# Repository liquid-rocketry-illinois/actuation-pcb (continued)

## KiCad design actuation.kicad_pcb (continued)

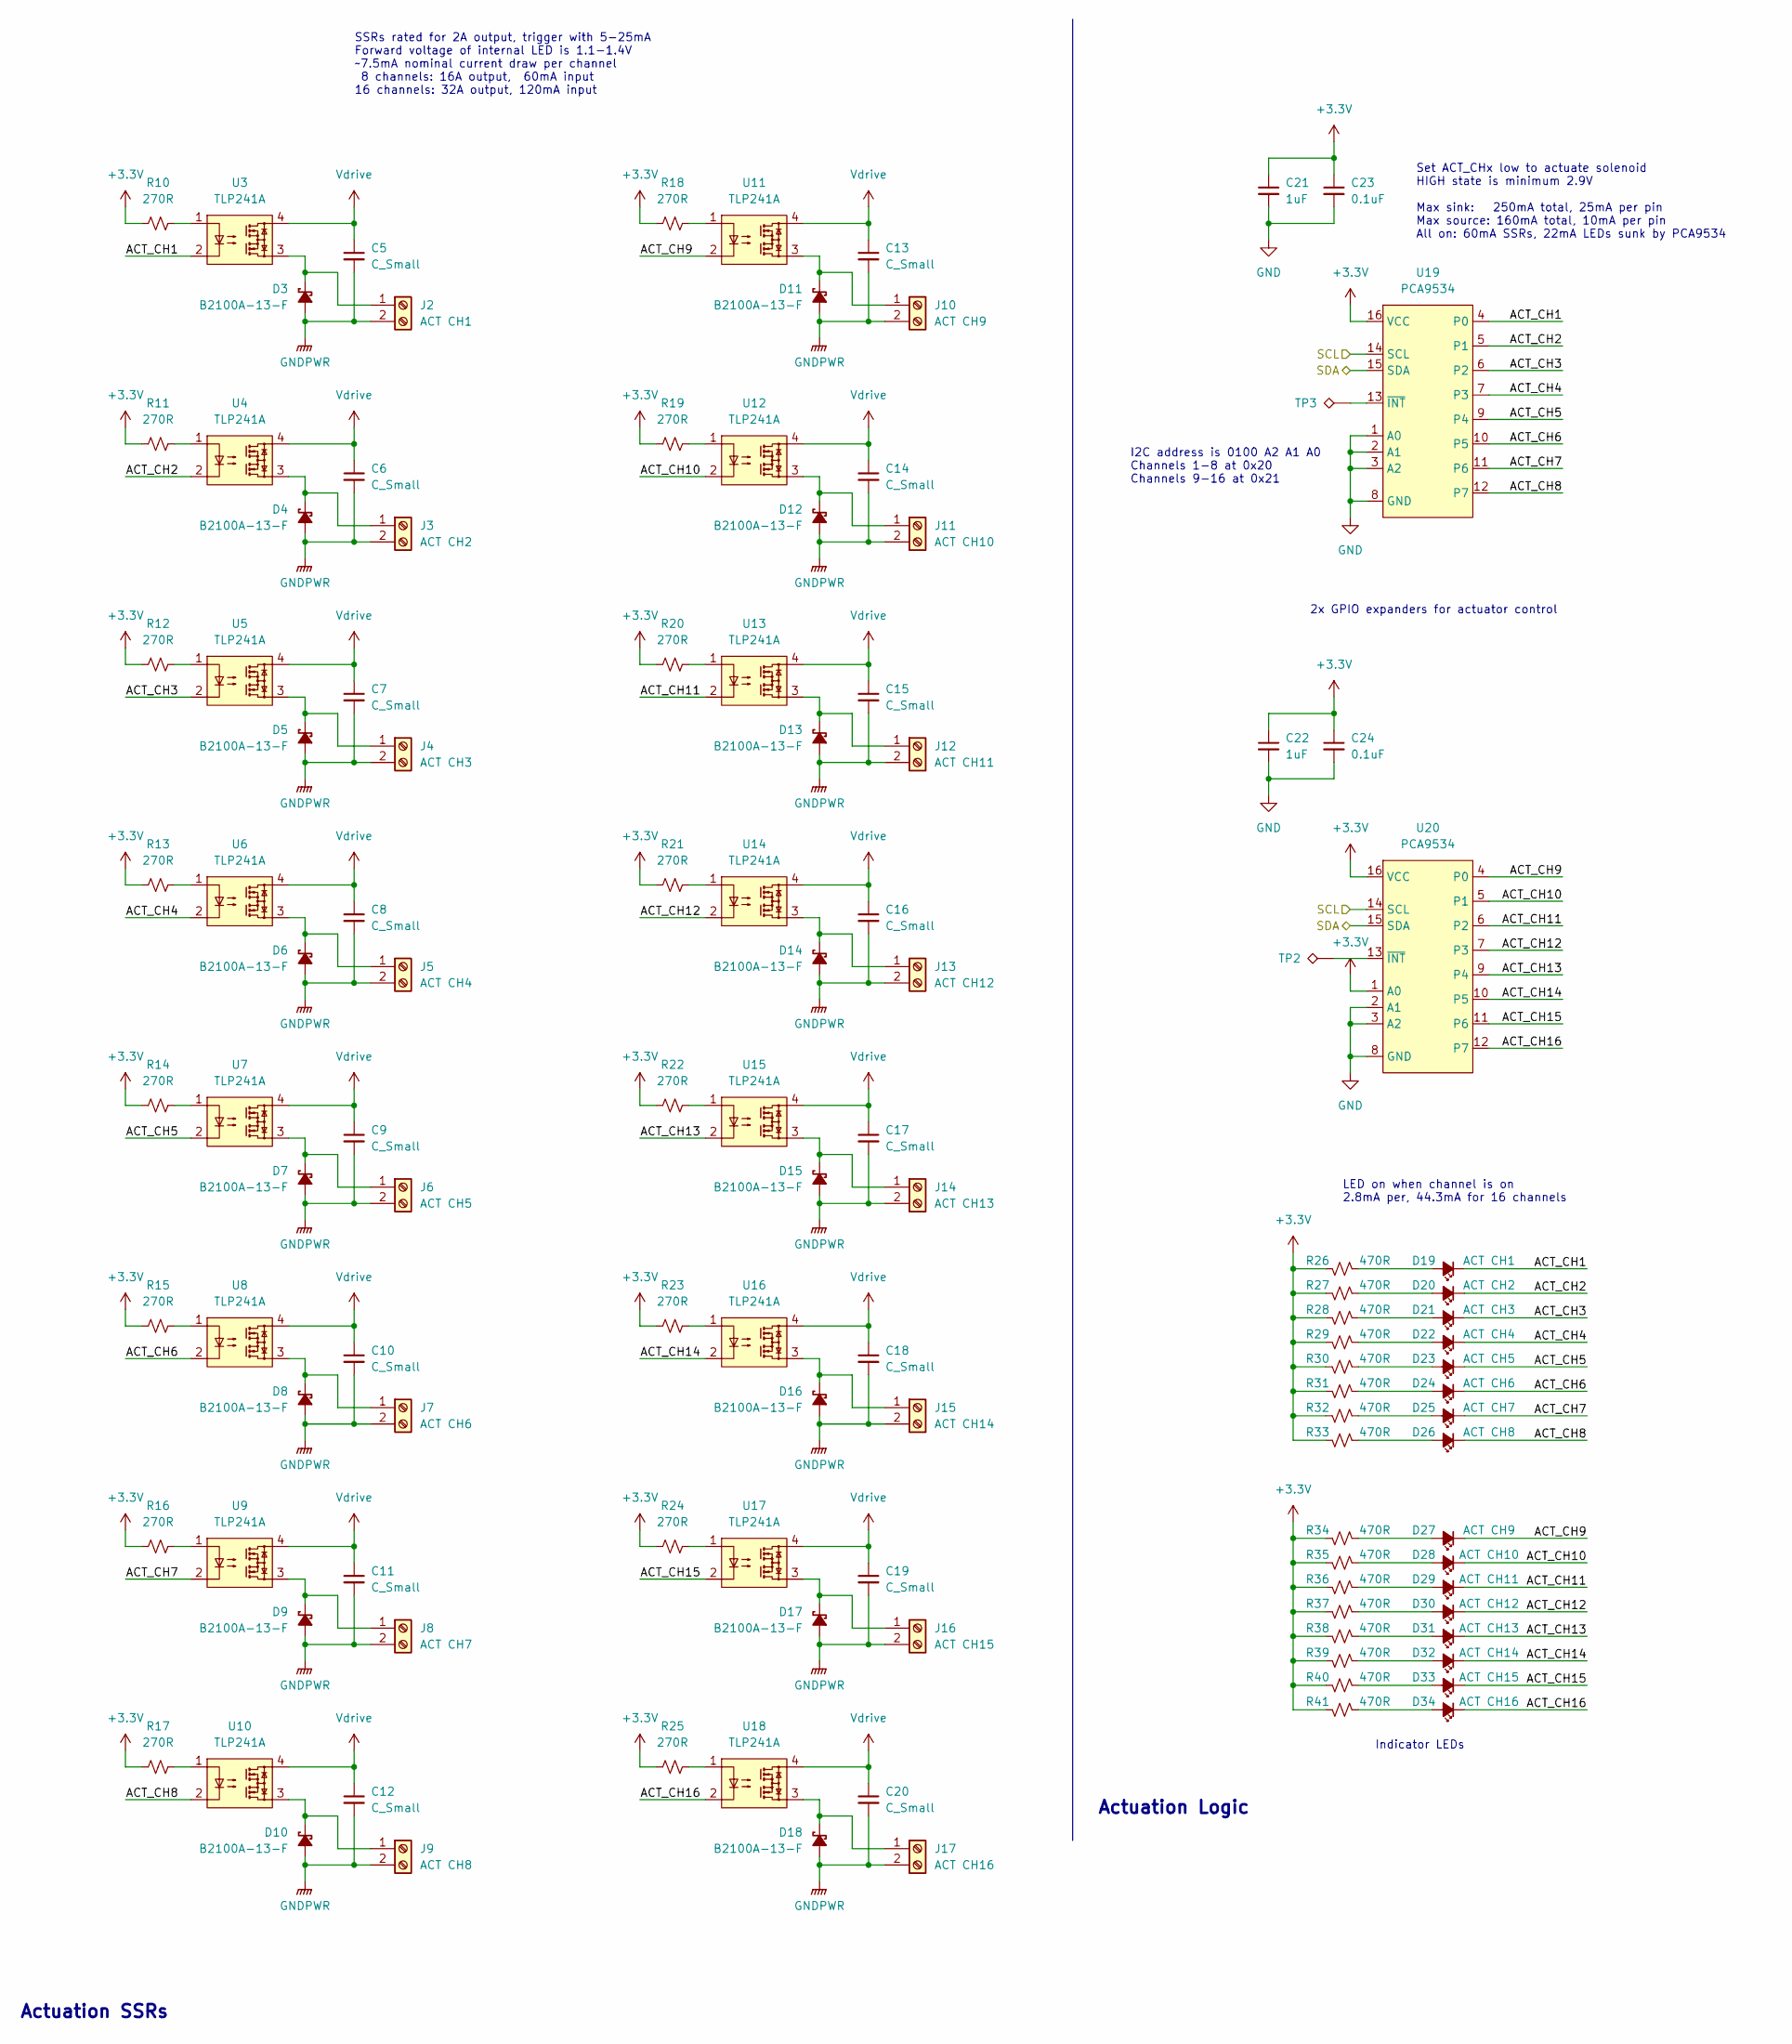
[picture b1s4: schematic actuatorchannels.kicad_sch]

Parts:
C5, C6, C7, C8, C9, C10, C11, C12, C13, C14, C15, C16, C17, C18, C19, C20: C_Small; C_1210_3225Metric; MPN CL32B106KBJNNWE
C21, C22: 1uF; C_0603_1608Metric
C23, C24: 0.1uF; C_0603_1608Metric
D3, D4, D5, D6, D7, D8, D9, D10, D11, D12, D13, D14, D15, D16, D17, D18: B2100A-13-F; D_SMA; MPN B2100A-13-F
D19: ACT CH1; LED_0603_1608Metric; MPN LTST-C191KFKT
D20: ACT CH2; LED_0603_1608Metric; MPN LTST-C191KFKT
D21: ACT CH3; LED_0603_1608Metric; MPN LTST-C191KFKT
D22: ACT CH4; LED_0603_1608Metric; MPN LTST-C191KFKT
D23: ACT CH5; LED_0603_1608Metric; MPN LTST-C191KFKT
D24: ACT CH6; LED_0603_1608Metric; MPN LTST-C191KFKT
D25: ACT CH7; LED_0603_1608Metric; MPN LTST-C191KFKT
D26: ACT CH8; LED_0603_1608Metric; MPN LTST-C191KFKT
D27: ACT CH9; LED_0603_1608Metric; MPN LTST-C191KFKT
D28: ACT CH10; LED_0603_1608Metric; MPN LTST-C191KFKT
D29: ACT CH11; LED_0603_1608Metric; MPN LTST-C191KFKT
D30: ACT CH12; LED_0603_1608Metric; MPN LTST-C191KFKT
D31: ACT CH13; LED_0603_1608Metric; MPN LTST-C191KFKT
D32: ACT CH14; LED_0603_1608Metric; MPN LTST-C191KFKT
D33: ACT CH15; LED_0603_1608Metric; MPN LTST-C191KFKT
D34: ACT CH16; LED_0603_1608Metric; MPN LTST-C191KFKT
J2: ACT CH1; XT30U-M; MPN XT30U-M
J3: ACT CH2; XT30U-M; MPN XT30U-M
J4: ACT CH3; XT30U-M; MPN XT30U-M
J5: ACT CH4; XT30U-M; MPN XT30U-M
J6: ACT CH5; XT30U-M; MPN XT30U-M
J7: ACT CH6; XT30U-M; MPN XT30U-M
J8: ACT CH7; XT30U-M; MPN XT30U-M
J9: ACT CH8; XT30U-M; MPN XT30U-M
J10: ACT CH9; XT30U-M; MPN XT30U-M
J11: ACT CH10; XT30U-M; MPN XT30U-M
J12: ACT CH11; XT30U-M; MPN XT30U-M
J13: ACT CH12; XT30U-M; MPN XT30U-M
J14: ACT CH13; XT30U-M; MPN XT30U-M
J15: ACT CH14; XT30U-M; MPN XT30U-M
J16: ACT CH15; XT30U-M; MPN XT30U-M
J17: ACT CH16; XT30U-M; MPN XT30U-M
R10, R11, R12, R13, R14, R15, R16, R17, R18, R19, R20, R21, R22, R23, R24, R25: 270R; R_0603_1608Metric; MPN RC0603FR-07270RL
R26, R27, R28, R29, R30, R31, R32, R33, R34, R35, R36, R37, R38, R39, R40, R41: 470R; R_0603_1608Metric
TP2, TP3: TestPoint_Alt; TestPoint_Pad_D2.0mm
U3, U4, U5, U6, U7, U8, U9, U10, U11, U12, U13, U14, U15, U16, U17, U18: TLP241A; MPN TLP241A(TP1,F
U19, U20: PCA9534; TSSOP-16_4.4x5mm_P0.65mm; MPN PCA9534PWR

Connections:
+3.3V: C21.1, C22.1, C23.1, C24.1, R10.1, R11.1, R12.1, R13.1, R14.1, R15.1, R16.1, R17.1, R18.1, R19.1, R20.1, R21.1, R22.1, R23.1, R24.1, R25.1, R26.1, R27.1, R28.1, R29.1, R30.1, R31.1, R32.1, R33.1, R34.1, R35.1, R36.1, R37.1, R38.1, R39.1, R40.1, R41.1, U19.16 (VCC), U20.1 (A0), U20.16 (VCC); also elsewhere on the board
/Actuator Channels/ACT_CH1: D19.1 (K), U3.2, U19.4 (P0)
/Actuator Channels/ACT_CH2: D20.1 (K), U4.2, U19.5 (P1)
/Actuator Channels/ACT_CH3: D21.1 (K), U5.2, U19.6 (P2)
/Actuator Channels/ACT_CH4: D22.1 (K), U6.2, U19.7 (P3)
/Actuator Channels/ACT_CH5: D23.1 (K), U7.2, U19.9 (P4)
/Actuator Channels/ACT_CH6: D24.1 (K), U8.2, U19.10 (P5)
/Actuator Channels/ACT_CH7: D25.1 (K), U9.2, U19.11 (P6)
/Actuator Channels/ACT_CH8: D26.1 (K), U10.2, U19.12 (P7)
/Actuator Channels/ACT_CH9: D27.1 (K), U11.2, U20.4 (P0)
/Actuator Channels/ACT_CH10: D28.1 (K), U12.2, U20.5 (P1)
/Actuator Channels/ACT_CH11: D29.1 (K), U13.2, U20.6 (P2)
/Actuator Channels/ACT_CH12: D30.1 (K), U14.2, U20.7 (P3)
/Actuator Channels/ACT_CH13: D31.1 (K), U15.2, U20.9 (P4)
/Actuator Channels/ACT_CH14: D32.1 (K), U16.2, U20.10 (P5)
/Actuator Channels/ACT_CH15: D33.1 (K), U17.2, U20.11 (P6)
/Actuator Channels/ACT_CH16: D34.1 (K), U18.2, U20.12 (P7)
/SCL: U19.14 (SCL), U20.14 (SCL); also elsewhere on the board
/SDA: U19.15 (SDA), U20.15 (SDA); also elsewhere on the board
GND: C21.2, C22.2, C23.2, C24.2, U19.1 (A0), U19.2 (A1), U19.3 (A2), U19.8 (GND), U20.2 (A1), U20.3 (A2), U20.8 (GND); also elsewhere on the board
GNDPWR: C5.2, C6.2, C7.2, C8.2, C9.2, C10.2, C11.2, C12.2, C13.2, C14.2, C15.2, C16.2, C17.2, C18.2, C19.2, C20.2, D3.2 (A), D4.2 (A), D5.2 (A), D6.2 (A), D7.2 (A), D8.2 (A), D9.2 (A), D10.2 (A), D11.2 (A), D12.2 (A), D13.2 (A), D14.2 (A), D15.2 (A), D16.2 (A), D17.2 (A), D18.2 (A), J2.2, J3.2, J4.2, J5.2, J6.2, J7.2, J8.2, J9.2, J10.2, J11.2, J12.2, J13.2, J14.2, J15.2, J16.2, J17.2; also elsewhere on the board
unnamed: D3.1 (K), J2.1, U3.3
unnamed: D4.1 (K), J3.1, U4.3
unnamed: D5.1 (K), J4.1, U5.3
unnamed: D6.1 (K), J5.1, U6.3
unnamed: D7.1 (K), J6.1, U7.3
unnamed: D8.1 (K), J7.1, U8.3
unnamed: D9.1 (K), J8.1, U9.3
unnamed: D10.1 (K), J9.1, U10.3
unnamed: D11.1 (K), J10.1, U11.3
unnamed: D12.1 (K), J11.1, U12.3
unnamed: D13.1 (K), J12.1, U13.3
unnamed: D14.1 (K), J13.1, U14.3
unnamed: D15.1 (K), J14.1, U15.3
unnamed: D16.1 (K), J15.1, U16.3
unnamed: D17.1 (K), J16.1, U17.3
unnamed: D18.1 (K), J17.1, U18.3
unnamed: D19.2 (A), R26.2
unnamed: D20.2 (A), R27.2
unnamed: D21.2 (A), R28.2
unnamed: D22.2 (A), R29.2
unnamed: D23.2 (A), R30.2
unnamed: D24.2 (A), R31.2
unnamed: D25.2 (A), R32.2
unnamed: D26.2 (A), R33.2
unnamed: D27.2 (A), R34.2
unnamed: D28.2 (A), R35.2
unnamed: D29.2 (A), R36.2
unnamed: D30.2 (A), R37.2
unnamed: D31.2 (A), R38.2
unnamed: D32.2 (A), R39.2
unnamed: D33.2 (A), R40.2
unnamed: D34.2 (A), R41.2
unnamed: R10.2, U3.1
unnamed: R11.2, U4.1
unnamed: R12.2, U5.1
unnamed: R13.2, U6.1
unnamed: R14.2, U7.1
unnamed: R15.2, U8.1
unnamed: R16.2, U9.1
unnamed: R17.2, U10.1
unnamed: R18.2, U11.1
unnamed: R19.2, U12.1
unnamed: R20.2, U13.1
unnamed: R21.2, U14.1
unnamed: R22.2, U15.1
unnamed: R23.2, U16.1
unnamed: R24.2, U17.1
unnamed: R25.2, U18.1
unnamed: TP2.1, U20.13 (~INT)
unnamed: TP3.1, U19.13 (~INT)
Vdrive: C5.1, C6.1, C7.1, C8.1, C9.1, C10.1, C11.1, C12.1, C13.1, C14.1, C15.1, C16.1, C17.1, C18.1, C19.1, C20.1, U3.4, U4.4, U5.4, U6.4, U7.4, U8.4, U9.4, U10.4, U11.4, U12.4, U13.4, U14.4, U15.4, U16.4, U17.4, U18.4; also elsewhere on the board

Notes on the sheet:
LED on when channel is on 2.8mA per, 44.3mA for 16 channels
SSRs rated for 2A output, trigger with 5-25mA Forward voltage of internal LED is 1.1-1.4V ~7.5mA nominal current draw per channel 8 channels: 16A output, 60mA input 16 channels: 32A output, 120mA input
Indicator LEDs
Actuation Logic
Actuation SSRs
2x GPIO expanders for actuator control
I2C address is 0100 A2 A1 A0 Channels 1-8 at 0x20 Channels 9-16 at 0x21
Set ACT_CHx low to actuate solenoid HIGH state is minimum 2.9V Max sink: 250mA total, 25mA per pin Max source: 160mA total, 10mA per pin All on: 60mA SSRs, 22mA LEDs sunk by PCA9534

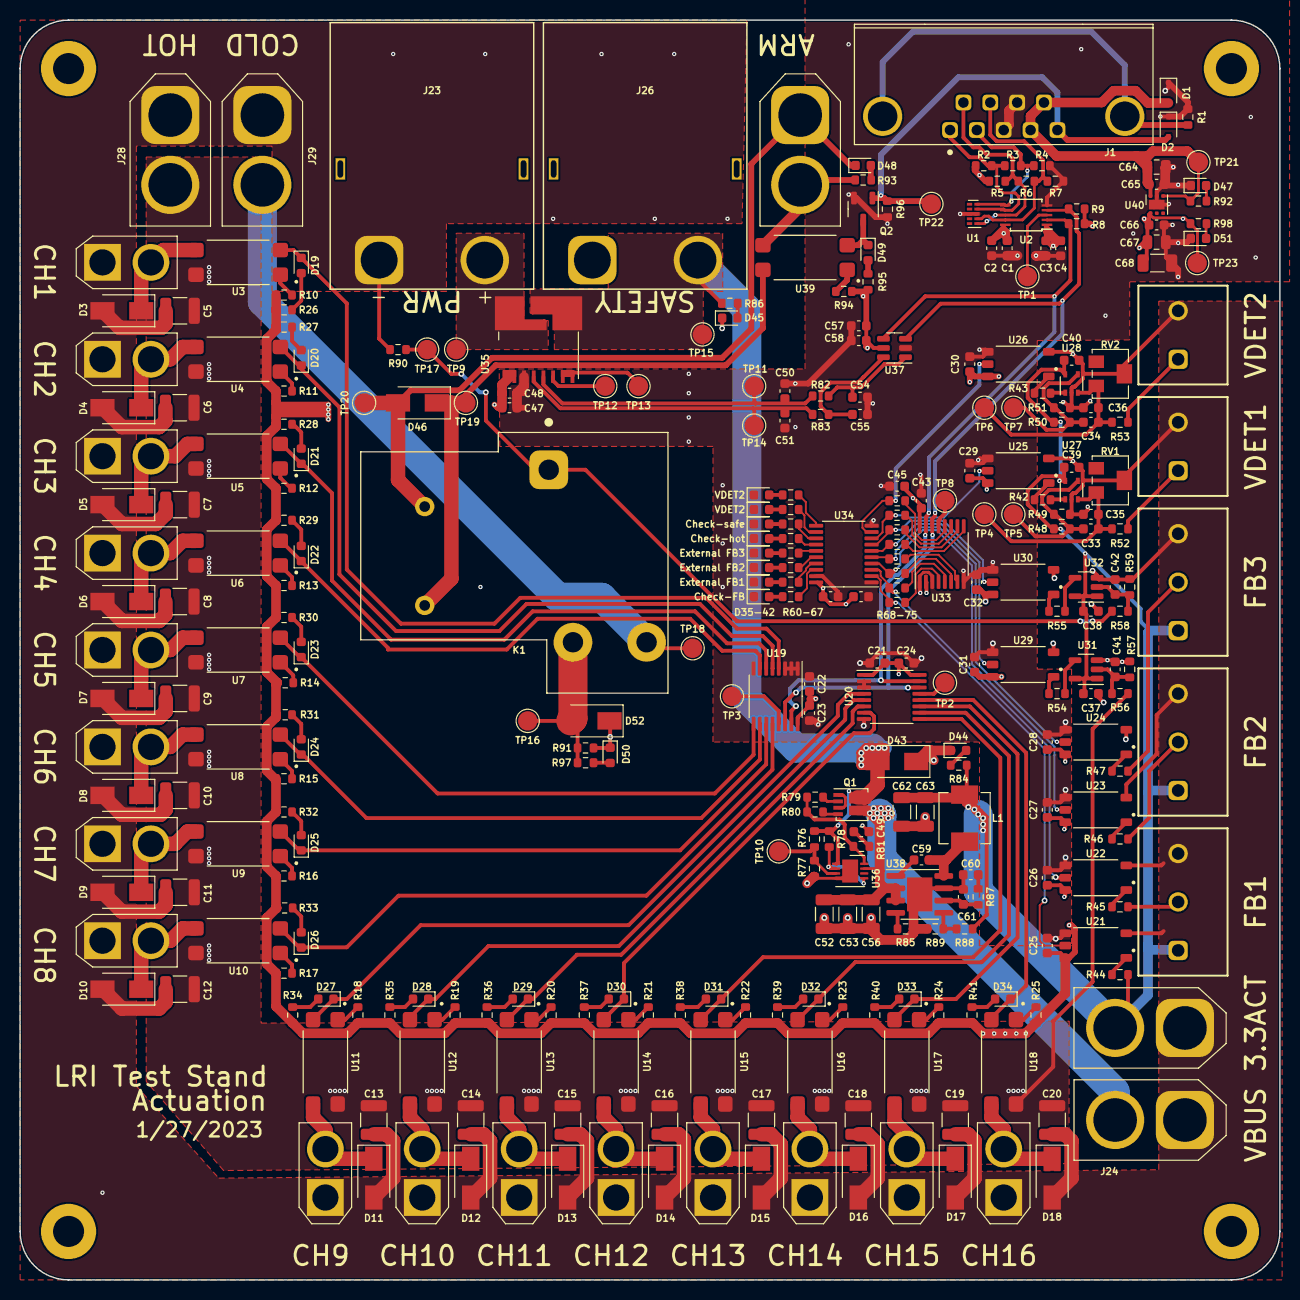
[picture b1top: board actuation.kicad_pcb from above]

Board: 4 copper layers, 130.0 x 130.0 mm, 316 parts (0 on the bottom side), 173 nets.

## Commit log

2022-10-11 KiCAD starter files
2022-10-31 RI2C, digital isolator, currents sense symbols
2022-11-03 GPIO, ADC
2022-11-07 made symbols for ssr, optocoupler (missing footprint)
2022-11-14 Finished optocoupler, and ssr
2022-11-14 Worked on schematic, symbol placement weird
2022-12-13 Added more symbols to schematic
2022-12-14 Grid issues
2022-12-14 added db9 and 3.3buck
2022-12-31 Cleaned up J115F11C symbol
2022-12-31 Cleaned up PCA9534 symbol
2022-12-31 Cleaned up TLP241A symbol
2022-12-31 Cleaned up TLI4971 symbol
2023-01-01 Added TLP2366 isolator
2023-01-01 Added TLV7031 symbol
2023-01-01 Added TPS70933 symbol
2023-01-01 Starting rework of schematic
2023-01-01 Array of SSRs for actuation channels
2023-01-01 Actuator channels complete
2023-01-01 Array of isolators for feedback channels
2023-01-01 Progress on feedback channels
2023-01-02 Voltage threshold detection feedback channels
2023-01-02 Feedback channels and status LEDs
2023-01-02 Power subsheet
2023-01-02 Fixed actuator channels to make GPIO expander sink instead of source current
2023-01-02 Check-safe channel with buffer
2023-01-02 Preliminary power scheme
2023-01-02 Added actuation status LEDs
2023-01-03 ADC filtering and decoupling for current sense
2023-01-03 add text
2023-01-03 Created arming circuit controllable by C&C
2023-01-03 Added hot-side supply protection
2023-01-03 Replaced hot-side feedback LDO with buck converter
2023-01-03 Reorganizing schematic
2023-01-03 More reorganizing
2023-01-03 Terminal block part selections
2023-01-03 more notes, generate pdf
2023-01-03 notes on feedback sheet
2023-01-03 estimate 3.3V current consumption
2023-01-03 schematic pdf
2023-01-03 labeled chips with their function
2023-01-03 labeled chips with their function- update pdf
2023-01-04 Added feedback indicator LED buffer and made changes to notes
2023-01-04 Footprints, some part selection, external power outputs
2023-01-04 Schematic reorganization
2023-01-05 TVS diodes for ESD protection on inputs
2023-01-05 Added power protection as well
2023-01-05 LED MPNs and new status indicator
2023-01-05 Changed status LED configuration
2023-01-05 Safing jumper, status LEDs, better naming of power states
2023-01-06 Fixing up footprints
2023-01-06 More terminal block footprint work
2023-01-06 MPN reassignment
2023-01-06 Added 3D models
2023-01-06 Experimentation with placement
2023-01-06 More placement
2023-01-07 Group components
2023-01-11 Modified de-safing key arrangement
2023-01-16 Check-safe channel, footprint changes
2023-01-16 Discharge resistors
2023-01-17 Test pads and TVS diode for drive voltage
2023-01-22 placed power parts
2023-01-22 3D models, footprint updates, general board layout
2023-01-23 arranged actuators, feedback
2023-01-23 much denser, should be no stray footprints now
2023-01-23 moved whole thing to center of page
2023-01-24 arranged power supplies
2023-01-24 roughly determine board outline
2023-01-24 100x130
2023-01-24 Revert "100x130"
    This reverts commit c49d85ffcdfed8898d048473301597551dfc5cab.
2023-01-26 Deleted some test points
2023-01-27 130x130 and arranged feedback
2023-01-27 1.5mm labels
2023-01-27 2mm CHx labeling
2023-01-27 routed a feedback leds
2023-01-27 copper power polygons
2023-01-27 adjust a few silkscreens
2023-01-30 Placement and silkscreen changes
2023-02-25 routed supplies and feedback
2023-03-01 feedback routing
2023-03-01 almost all connected
2023-03-01 everything connected
2023-03-01 no drc errors, still need silkscreen and check current paths
2023-03-02 cameron adjustments, 3.3 plane
2023-03-04 moved some traces
2023-03-05 fix silkscreens, planes
2023-03-11 Small updates
2023-03-13 stitching vias
2023-03-22 Routing touch-ups, silkscreen changes, finalized labels, adjusted power planes
2023-03-22 Gerbers and passive value update
2023-04-03 Finishing up part selection
2023-04-03 Updated BOM
2023-04-03 filled digikey mpn and inventory:
2023-04-05 Updated BOM for ordering
2023-05-01 generate ibom:
2024-07-15 generate schematic pdf
